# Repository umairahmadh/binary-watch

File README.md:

# binary-watch
 
Based on https://www.instructables.com/The-Ultimate-Binary-Watch/

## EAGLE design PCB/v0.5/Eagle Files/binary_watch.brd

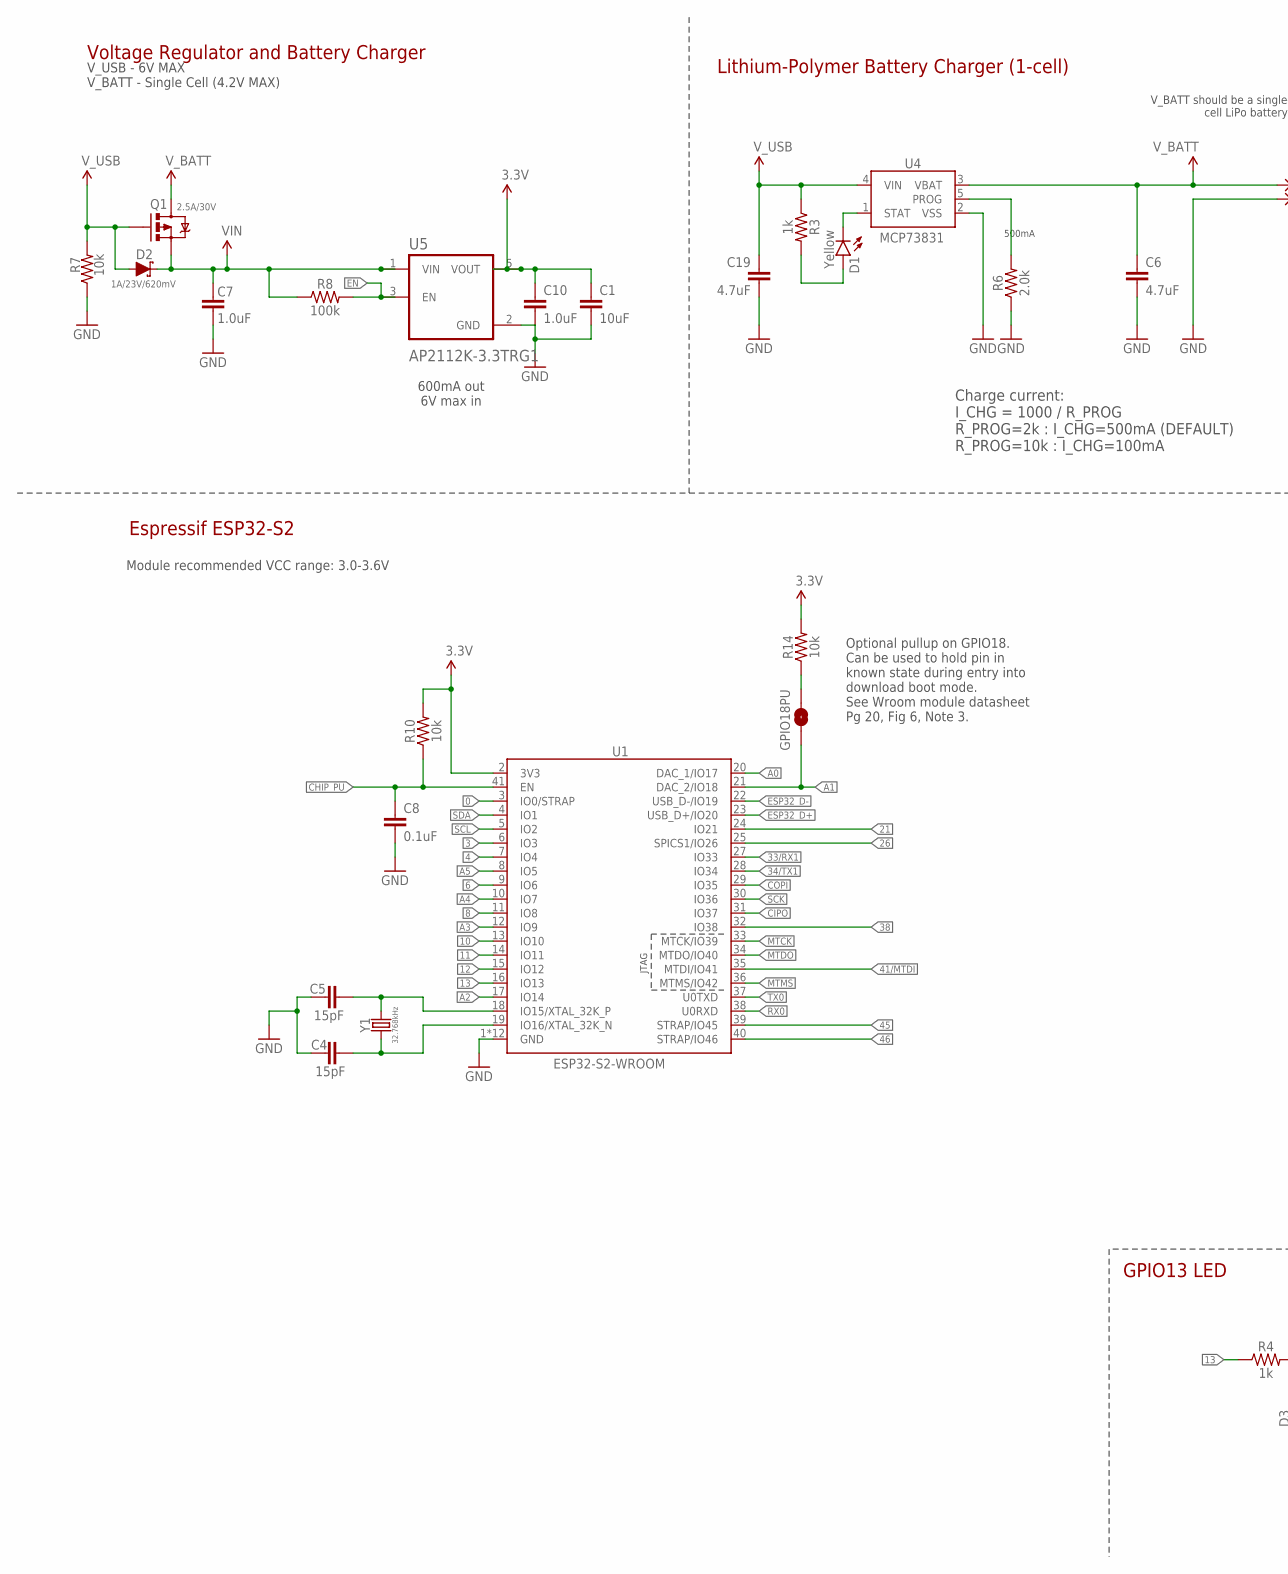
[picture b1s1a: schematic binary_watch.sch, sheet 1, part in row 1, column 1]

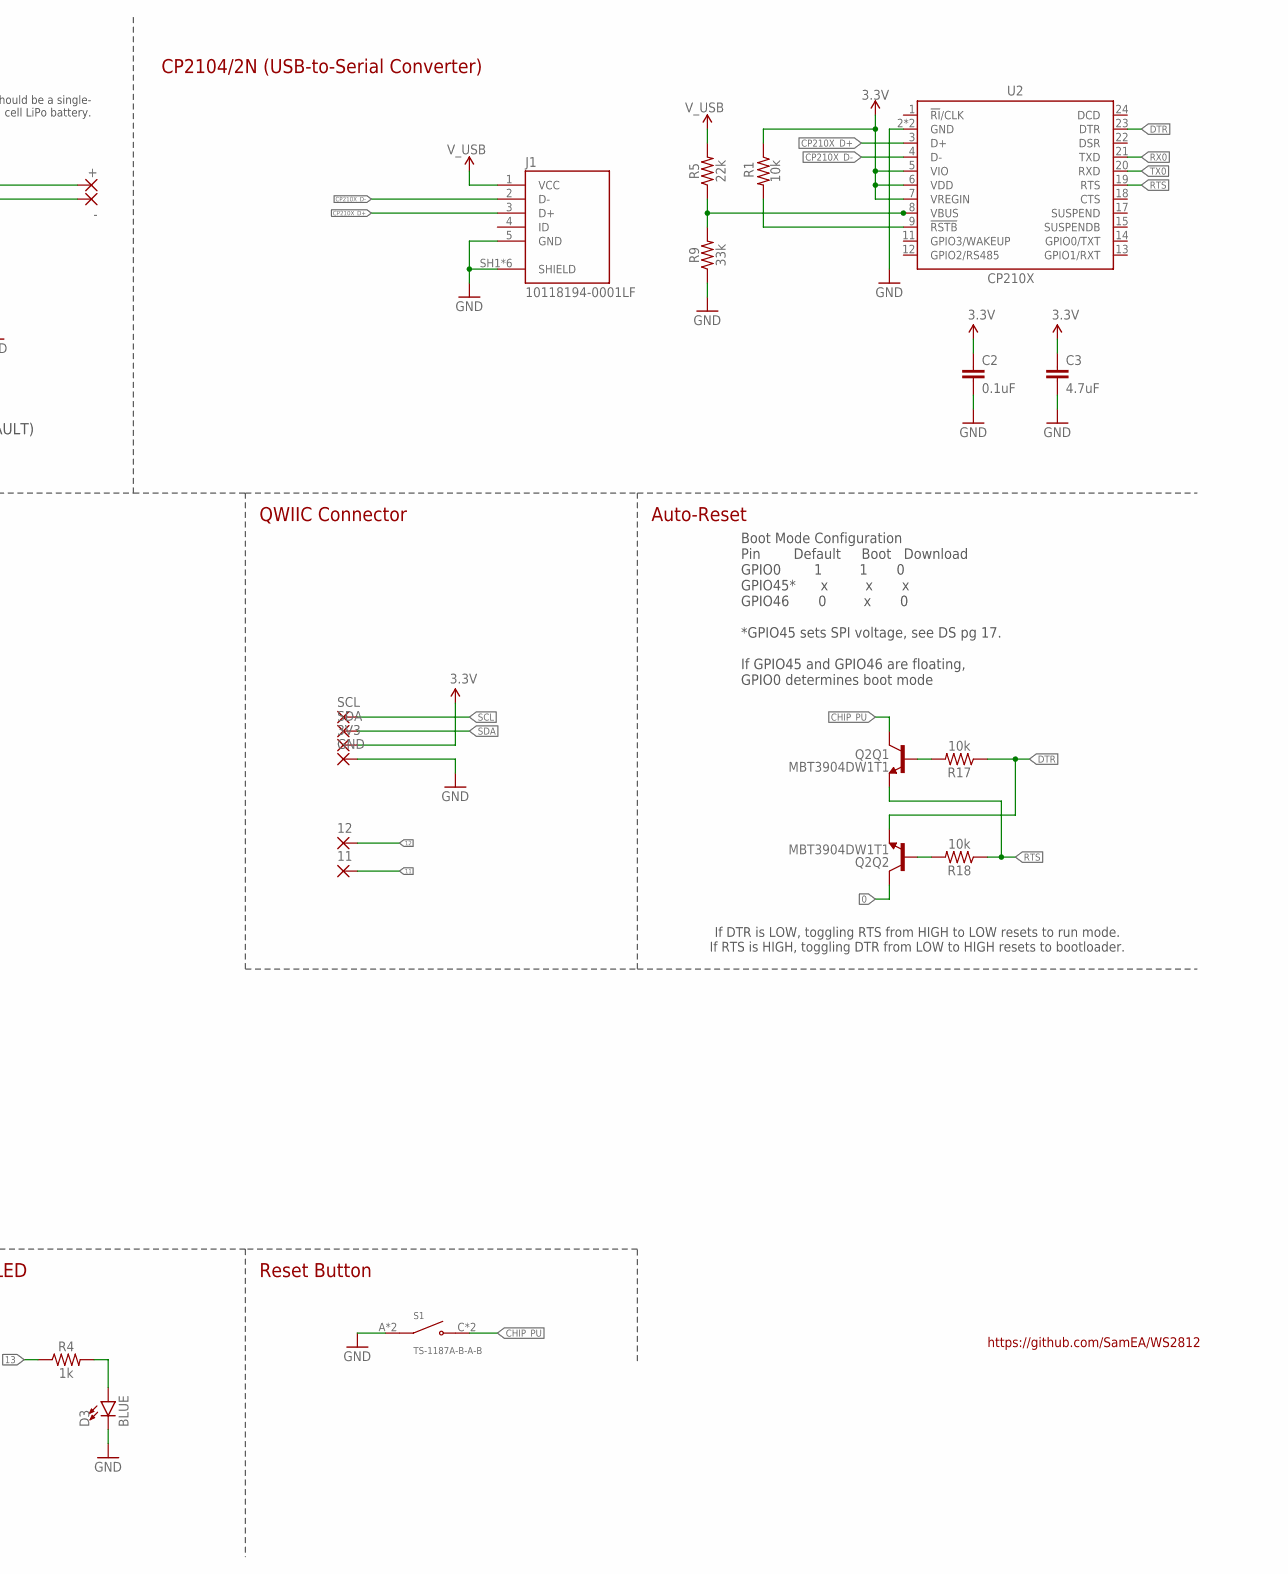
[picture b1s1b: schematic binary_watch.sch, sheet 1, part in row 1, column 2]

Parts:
3V3, 11, 12: 1,6/0,8
+: WIREPAD1,6/0,8; 1,6/0,8
-: WIREPAD1,6/0,8; 1,6/0,8
C1: 10uF; 0402-TIGHT
C2, C8: 0.1uF; 0402-TIGHT
C3, C6, C19: 4.7uF; 0402-TIGHT
C4, C5: 15pF; 0402-TIGHT
C7, C10: 1.0uF; 0402-TIGHT
D1: Yellow; LED-0603
D2: 1A/23V/620mV; SOD-323
D3: BLUE; LED-0603
GND: 1,6/0,8
GPIO18PU: JUMPER-SMT_2_NO_SILK; SMT-JUMPER_2_NO_SILK
J1: 10118194-0001LF; AMPHENOL_10118194-0001LF
Q1: 2.5A/30V; SOT23-3@1
Q2: MBT3904DW1T1; SC70-6
R1, R7, R10, R14, R17, R18: 10k; 0402-TIGHT
R3, R4: 1k; 0402-TIGHT
R5: 22k; 0402-TIGHT
R6: 2.0k; 0603
R8: 100k; 0402-TIGHT
R9: 33k; 0402-TIGHT
S1: TS-1187A-B-A-B; SW_TS-1187A-B-A-B
SCL: 1,6/0,8
SDA: 1,6/0,8
U1: ESP32-S2-WROOM
U2: CP210X; QFN24
U4: MCP73831; SOT23-5
U5: AP2112K-3.3TRG1; SOT95P285X140-5N
Y1: 32.768kHz; CRYSTAL-SMD-3.2X1.5MM

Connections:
0: Q2.6 (C), U1.3 (IO0/STRAP)
3: U1.6 (IO3)
3.3V: 3V3.1, C1.1, C2.1, C3.1, C10.1, R1.1, R10.2, R14.2, U1.2 (3V3), U2.5 (VIO), U2.6 (VDD), U2.7 (VREGIN), U5.5 (VOUT); also elsewhere on the board
4: U1.7 (IO4)
6: U1.9 (IO6)
8: U1.11 (IO8)
10: U1.13 (IO10)
11: 11.1, U1.14 (IO11); also elsewhere on the board
12: 12.1, U1.15 (IO12); also elsewhere on the board
13: R4.1, U1.16 (IO13)
21: U1.24 (IO21)
26: U1.25 (SPICS1/IO26)
33/RX1: U1.27 (IO33)
34/TX1: U1.28 (IO34)
38: U1.32 (IO38)
41/MTDI: U1.35 (MTDI/IO41)
45: U1.39 (STRAP/IO45)
46: U1.40 (STRAP/IO46)
A0: U1.20 (DAC_1/IO17)
A1: GPIO18PU.1, U1.21 (DAC_2/IO18)
A2: U1.17 (IO14)
A3: U1.12 (IO9)
A4: U1.10 (IO7)
A5: U1.8 (IO5)
CHG: D1.C, U4.1 (STAT)
CHIP_PU: C8.1, Q2.3 (C), R10.1, S1.C (NO), S1.D (NO), U1.41 (EN)
CIPO: U1.31 (IO37)
COPI: U1.29 (IO35)
CP210X_D+: J1.3 (D+), U2.3 (D+)
CP210X_D-: J1.2 (D-), U2.4 (D-)
DTR: Q2.1 (E), R17.1, U2.23 (DTR)
EN: R8.2, U5.3 (EN)
ESP32_D+: U1.23 (USB_D+/IO20)
ESP32_D-: U1.22 (USB_D-/IO19)
GND: -.1, C1.2, C2.2, C3.2, C4.1, C5.1, C6.2, C7.2, C8.2, C10.2, C19.2, D3.C, GND.1, J1.5 (GND), J1.SH1 (SHIELD), J1.SH2 (SHIELD), J1.SH3 (SHIELD), J1.SH4 (SHIELD), J1.SH5 (SHIELD), J1.SH6 (SHIELD), R6.1, R7.1, R9.1, S1.A (COM), S1.B (COM), U1.1 (GND), U1.26 (GND), U1.42 (GND), U1.GNDEP0 (GND), U1.GNDEP1 (GND), U1.GNDEP2 (GND), U1.GNDEP3 (GND), U1.GNDEP4 (GND), U1.GNDEP5 (GND), U1.GNDEP6 (GND), U1.GNDEP7 (GND), U1.GNDEP8 (GND), U2.2 (GND), U2.PAD (GND), U4.2 (VSS), U5.2 (GND); also elsewhere on the board
MTCK: U1.33 (MTCK/IO39)
MTDO: U1.34 (MTDO/IO40)
MTMS: U1.36 (MTMS/IO42)
unnamed: R1.2, U2.9 (!RSTB)
unnamed: D3.A, R4.2
unnamed: R5.1, R9.2, U2.8 (VBUS)
unnamed: C5.2, U1.18 (IO15/XTAL_32K_P), Y1.P$2 (2)
unnamed: C4.2, U1.19 (IO16/XTAL_32K_N), Y1.P$1 (1)
unnamed: R6.2, U4.5 (PROG)
unnamed: Q2.5 (B), R17.2
unnamed: Q2.2 (B), R18.2
unnamed: GPIO18PU.2, R14.1
unnamed: D1.A, R3.2
RTS: Q2.4 (E), R18.1, U2.19 (RTS)
RX0: U1.38 (U0RXD), U2.21 (TXD)
SCK: U1.30 (IO36)
SCL: SCL.1, U1.5 (IO2)
SDA: SDA.1, U1.4 (IO1)
TX0: U1.37 (U0TXD), U2.20 (RXD)
VIN: C7.1, D2.C, Q1.2 (S), R8.1, U5.1 (VIN)
V_BATT: +.1, C6.1, Q1.3 (D), U4.3 (VBAT)
V_USB: C19.1, D2.A, J1.1 (VCC), Q1.1 (G), R3.1, R5.2, R7.2, U4.4 (VIN)

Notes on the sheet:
Boot Mode Configuration Pin Default Boot Download GPIO0 1 1 0 GPIO45* x x x GPIO46 0 x 0 *GPIO45 sets SPI voltage, see DS pg 17. If GPIO45 and GPIO46 are floating, GPIO0 determines boot mode
CP2104/2N (USB-to-Serial Converter)
V_BATT should be a single- cell LiPo battery.
Charge current: I_CHG = 1000 / R_PROG R_PROG=2k : I_CHG=500mA (DEFAULT) R_PROG=10k : I_CHG=100mA
Voltage Regulator and Battery Charger
Lithium-Polymer Battery Charger (1-cell)
600mA out 6V max in
Auto-Reset
Espressif ESP32-S2
Reset Button
If DTR is LOW, toggling RTS from HIGH to LOW resets to run mode. If RTS is HIGH, toggling DTR from LOW to HIGH resets to bootloader.
QWIIC Connector
GPIO13 LED
V_USB - 6V MAX V_BATT - Single Cell (4.2V MAX)
500mA
Module recommended VCC range: 3.0-3.6V
Optional pullup on GPIO18. Can be used to hold pin in known state during entry into download boot mode. See Wroom module datasheet Pg 20, Fig 6, Note 3.
https://github.com/SamEA/WS2812

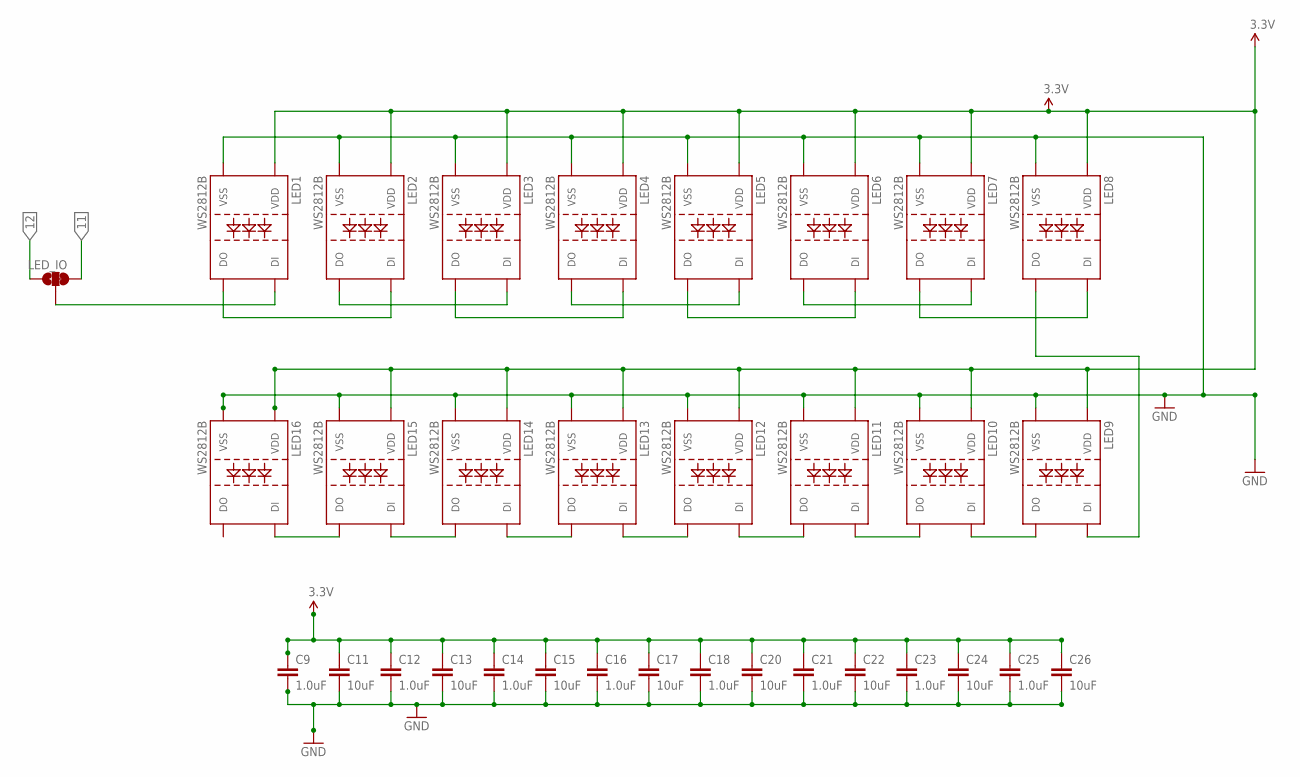
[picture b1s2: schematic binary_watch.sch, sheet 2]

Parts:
C9, C12, C14, C16, C18, C21, C23, C25: 1.0uF; 0402-TIGHT
C11, C13, C15, C17, C20, C22, C24, C26: 10uF; 0402-TIGHT
LED1, LED2, LED3, LED4, LED5, LED6, LED7, LED8, LED9, LED10, LED11, LED12, LED13, LED14, LED15, LED16: WS2812B
LED_IO: JUMPER-SMT_3_1-NC_TRACE_SILK; SMT-JUMPER_3_1-NC_TRACE_SILK

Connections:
3.3V: C9.1, C11.1, C12.1, C13.1, C14.1, C15.1, C16.1, C17.1, C18.1, C20.1, C21.1, C22.1, C23.1, C24.1, C25.1, C26.1, LED1.1 (VDD), LED2.1 (VDD), LED3.1 (VDD), LED4.1 (VDD), LED5.1 (VDD), LED6.1 (VDD), LED7.1 (VDD), LED8.1 (VDD), LED9.1 (VDD), LED10.1 (VDD), LED11.1 (VDD), LED12.1 (VDD), LED13.1 (VDD), LED14.1 (VDD), LED15.1 (VDD), LED16.1 (VDD); also elsewhere on the board
11: LED_IO.3; also elsewhere on the board
12: LED_IO.1; also elsewhere on the board
GND: C9.2, C11.2, C12.2, C13.2, C14.2, C15.2, C16.2, C17.2, C18.2, C20.2, C21.2, C22.2, C23.2, C24.2, C25.2, C26.2, LED1.3 (VSS), LED2.3 (VSS), LED3.3 (VSS), LED4.3 (VSS), LED5.3 (VSS), LED6.3 (VSS), LED7.3 (VSS), LED8.3 (VSS), LED9.3 (VSS), LED10.3 (VSS), LED11.3 (VSS), LED12.3 (VSS), LED13.3 (VSS), LED14.3 (VSS), LED15.3 (VSS), LED16.3 (VSS); also elsewhere on the board
unnamed: LED1.4 (DI), LED_IO.2
unnamed: LED1.2 (DO), LED2.4 (DI)
unnamed: LED2.2 (DO), LED3.4 (DI)
unnamed: LED3.2 (DO), LED4.4 (DI)
unnamed: LED4.2 (DO), LED5.4 (DI)
unnamed: LED5.2 (DO), LED6.4 (DI)
unnamed: LED6.2 (DO), LED7.4 (DI)
unnamed: LED7.2 (DO), LED8.4 (DI)
unnamed: LED8.2 (DO), LED9.4 (DI)
unnamed: LED9.2 (DO), LED10.4 (DI)
unnamed: LED10.2 (DO), LED11.4 (DI)
unnamed: LED11.2 (DO), LED12.4 (DI)
unnamed: LED12.2 (DO), LED13.4 (DI)
unnamed: LED13.2 (DO), LED14.4 (DI)
unnamed: LED14.2 (DO), LED15.4 (DI)
unnamed: LED15.2 (DO), LED16.4 (DI)

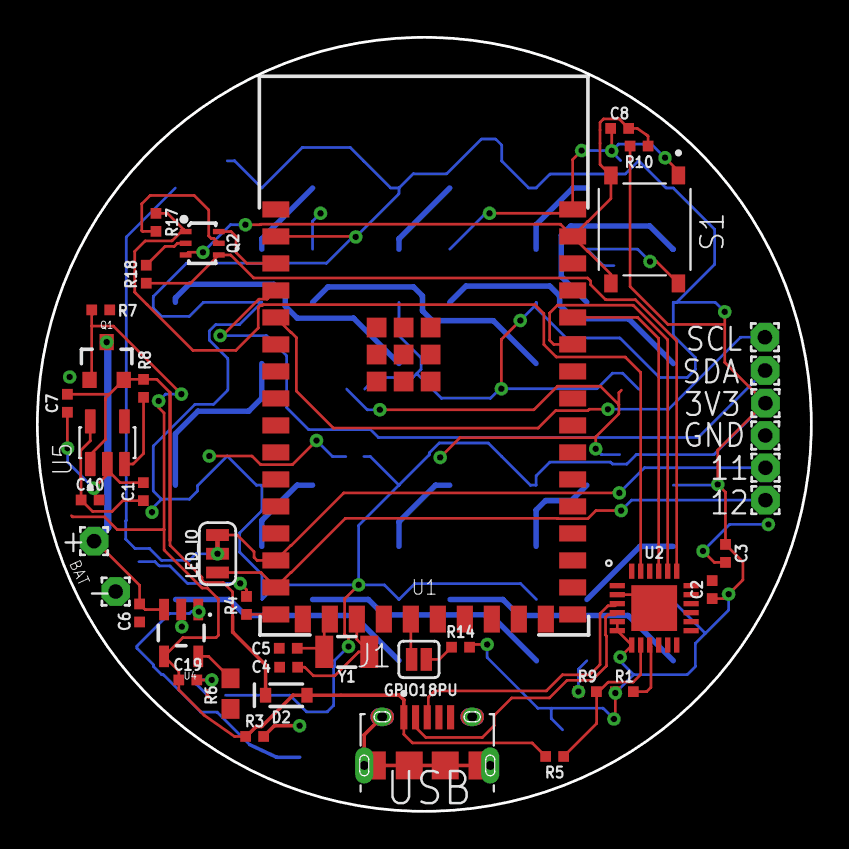
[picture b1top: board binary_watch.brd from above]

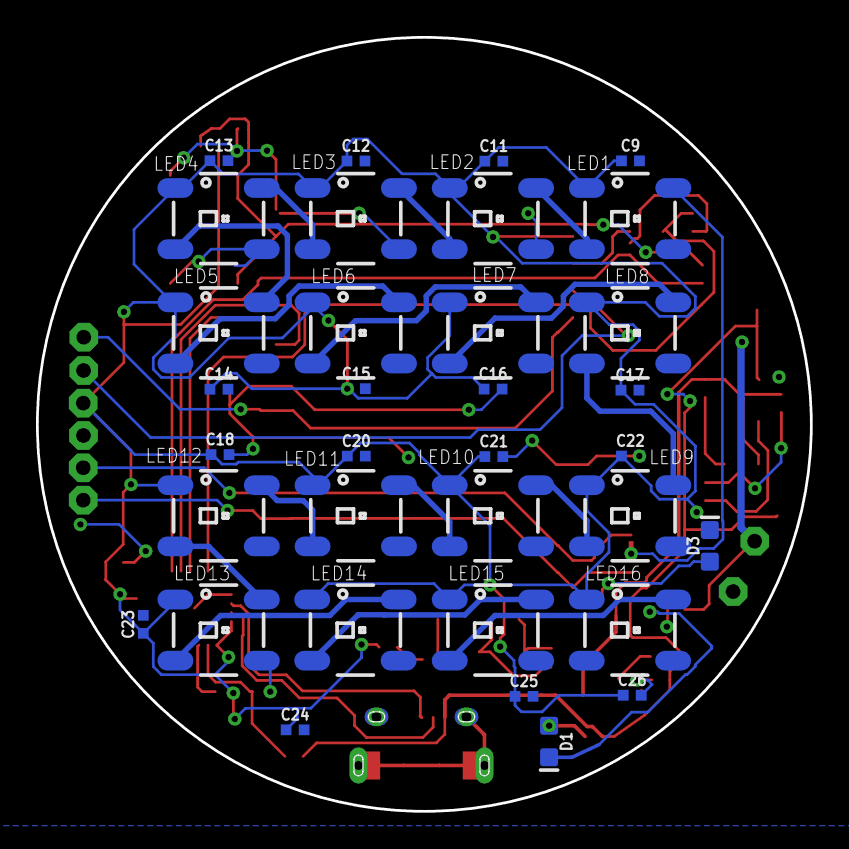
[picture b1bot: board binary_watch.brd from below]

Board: 2 copper layers, 43.0 x 43.0 mm, 76 parts (34 on the bottom side), 47 nets.

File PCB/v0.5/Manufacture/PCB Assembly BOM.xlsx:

Comment | Designator | Footprint | JLCPCB Part #（optional）
100uF | C1 | CAP-SMD_L3.5-W2.8 | C16133
15K | R5,R6 | R0603 | C22809
DC-005-20A_C136744 | DC1 | DC-IN-TH_DC-005-20A | C136744
Header-Female-2.54_1x8 | P2,P3 | HDR-TH_8P-P2.54-V | C27438
K2-1102DP-C4SW-04 | SW1 | KEY-TH_4P-L6.0-W6.0-P4.50-LS6.5 | C110153
ATMEGA328P-PU | U1 | DIP-28_L34.6-W7.3-P2.54-LS10.2-BL | C33901
6.70688E8 | USB1 | USB-B-TH_67068-8000 | C114097
0.1µF ceramic capacitors | C2, C8 | 0402-TIGHT
1µF ceramic capacitors | C7, C9, C10, C12, C14, C16, C18, C21, C23, C25 | 0402-TIGHT
100kΩ resistor | R8 | 0402-TIGHT
10kΩ resistor | R1, R7, R10, R14, R17, R18 | 0402-TIGHT
10.0µF ceramic capacitors | C1, C11, C13, C15, C17, C20, C22, C24, C26 | 0402-TIGHT
15pF ceramic capacitors | C4, C5 | 0402-TIGHT
Schottky diode | D2 | SOD-323
1kΩ resistor | R3, R4 | 0402-TIGHT
RES-08296 | R6 | 0603
Generic PMOSFET | Q1 | SOT23-3@1
22kΩ resistor | R5 | 0402-TIGHT
32.768kHz Crystal | Y1 | CRYSTAL-SMD-3.2X1.5MM
33kΩ resistor | R9 | 0402-TIGHT
4.7µF ceramic capacitors | C3, C6, C19 | 0402-TIGHT
Voltage Regulator LDO | U3 | SOT23-5
Blue SMD LED | D3 | LED-0603
 | U2 | QFN24
ESP32-S2-WROOM - trace antenna (includes keepout) | U1 | ESP32-S2-WROOM
Dual NPN Transistors in Single Package | Q2 | SC70-6
Miniature single cell, fully integrated Li-Ion, Li-polymer charge management co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 | U4 | SOT23-5
Micro USB B connector | U$1 | MICRO-USB
Momentary Switch (Pushbutton) - SPST - Two Circuits | S1 | TACTILE_SWITCH_SMD_4.6X2.8MM
RGB LEDs | LED1, LED2, LED3, LED4, LED5, LED6, LED7, LED8, LED9, LED10, LED11, LED12, LED1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 | WS2812B
Yellow SMD LED | D1 | LED-0603

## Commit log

2022-11-25 added files
2022-11-25 renamed src to pcb
2022-11-25 updated readme with instructable link
2022-12-04 Added more sections on the schematics, added library files.
2022-12-05 Completed Schematics
2022-12-31 component placement done
2024-06-29 add eagle files
2024-08-11 v0.5 finalised and ordered from JLC today

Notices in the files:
parts and their libraries:
SparkFun-Aesthetics: Licensing: Creative Commons ShareAlike 4.0 International - https://creativecommons.org/licenses/by-sa/4.0
